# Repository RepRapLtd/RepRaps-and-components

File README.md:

# RepRaps-and-components
Various designs for RepRaps and bits of them

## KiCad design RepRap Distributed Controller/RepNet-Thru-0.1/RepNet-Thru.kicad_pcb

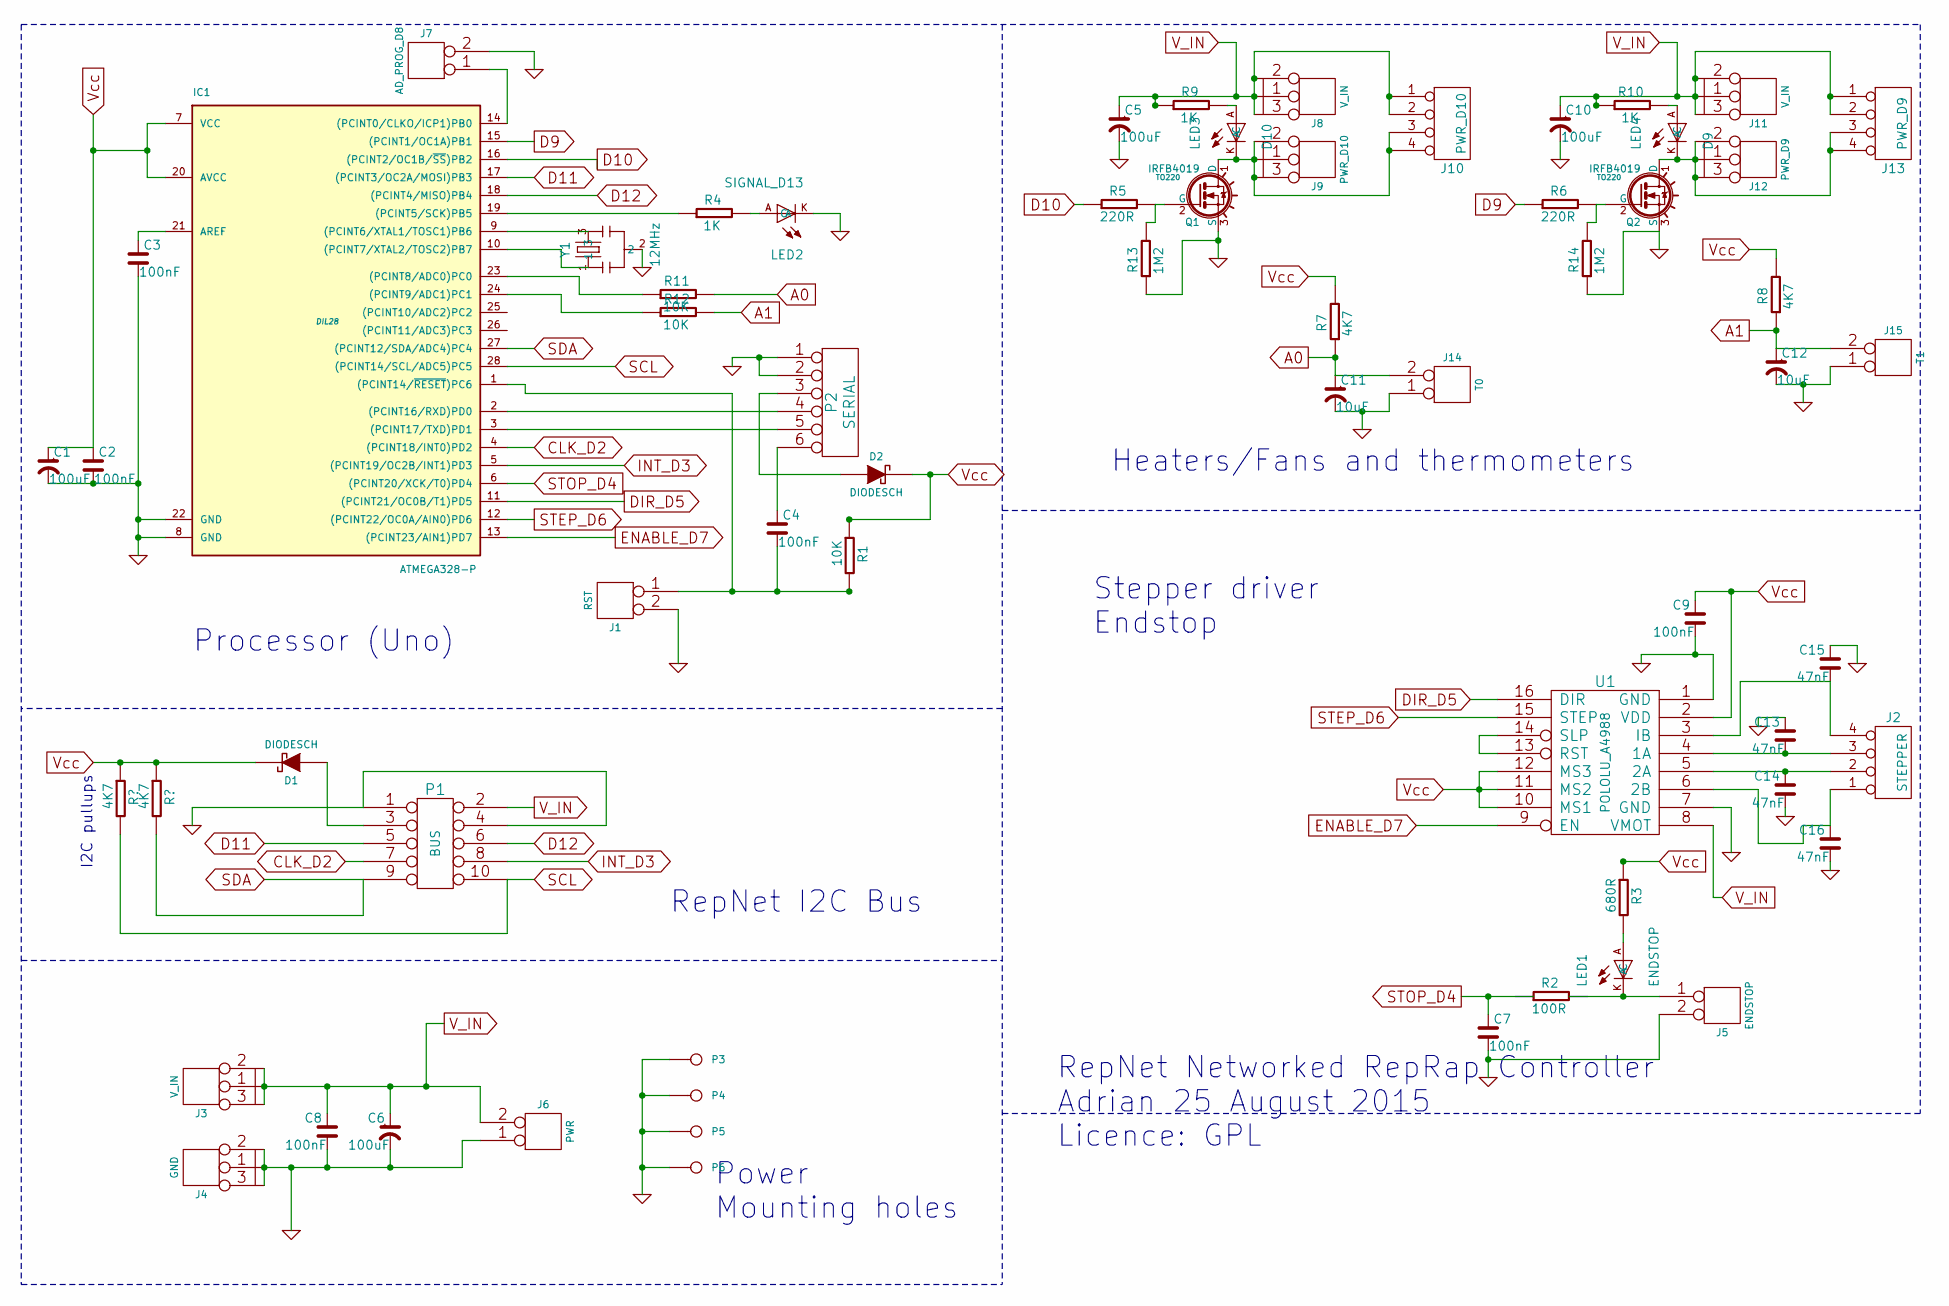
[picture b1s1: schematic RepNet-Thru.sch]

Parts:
C1, C5, C6, C10: 100uF
C2, C3, C4, C7, C8, C9: 100nF
C11, C12: 10uF
C13, C14, C15, C16: 47nF
D1, D2: DIODESCH
IC1: ATMEGA328-P; DIL28
J1: RST
J2: STEPPER
J3, J8, J11: V_IN
J4: GND
J5: ENDSTOP
J6: PWR
J7: AD_PROG_D8
J9, J10: PWR_D10
J12, J13: PWR_D9
J14: T0
J15: T1
LED1: ENDSTOP; SparkFun-LED3MM
LED2: SIGNAL_D13; SparkFun-LED3MM
LED3: D10; SparkFun-LED3MM
LED4: D9; SparkFun-LED3MM
P1: BUS
P2: SERIAL
P3, P4, P5, P6: mount
Q1, Q2: IRFB4019; TO220
R1, R11, R12: 10K
R2: 100R
R3: 680R
R4, R9, R10: 1K
R5, R6: 220R
R7, R8: 4K7
R13, R14: 1M2
U1: POLOLU_A4988
Y1: 12MHz; SparkFun-RESONATOR-PTH

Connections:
A0: C11.1, J14.2 (PM), R7.1, R11.2
A1: C12.1, J15.2 (PM), R8.1, R12.2
CLK_D2: IC1.4 ((PCINT18/INT0)PD2), P1.7
D9: IC1.15 ((PCINT1/OC1A)PB1), R6.1
D10: IC1.16 ((PCINT2/OC1B/~SS~)PB2), R5.1
D11: IC1.17 ((PCINT3/OC2A/MOSI)PB3), P1.5
D12: IC1.18 ((PCINT4/MISO)PB4), P1.6
DIR_D5: IC1.11 ((PCINT21/OC0B/T1)PD5), U1.16 (DIR)
ENABLE_D7: IC1.13 ((PCINT23/AIN1)PD7), U1.9 (EN)
GND: C1.2, C2.2, C3.2, C5.2, C6.2, C7.2, C8.2, C9.2, C10.2, C11.2, C12.2, C13.1, C14.2, C15.1, C16.2, IC1.8 (GND), IC1.22 (GND), J1.2 (PM), J4.1, J4.2, J4.3, J5.2 (PM), J6.1, J7.2 (PM), J14.1, J15.1, LED2.K (C), P1.1, P1.4, P2.1, P2.2, P3.1, P4.1, P5.1, P6.1, Q1.3 (S), Q2.3 (S), R13.1, R14.1, U1.1 (GND), U1.7 (GND), Y1.2
INT_D3: IC1.5 ((PCINT19/OC2B/INT1)PD3), P1.8
unnamed: IC1.10 ((PCINT7/XTAL2/TOSC2)PB7), Y1.1
unnamed: IC1.9 ((PCINT6/XTAL1/TOSC1)PB6), Y1.3
unnamed: IC1.3 ((PCINT17/TXD)PD1), P2.5
unnamed: IC1.2 ((PCINT16/RXD)PD0), P2.4
unnamed: D2.1 (A), P2.3
unnamed: IC1.14 ((PCINT0/CLKO/ICP1)PB0), J7.1
unnamed: C4.2, IC1.1 ((PCINT14/~RESET~)PC6), J1.1, R1.2
unnamed: C4.1, P2.6
unnamed: U1.13 (RST), U1.14 (SLP)
unnamed: C3.1, IC1.21 (AREF)
unnamed: D1.1 (A), P1.3
unnamed: LED2.A, R4.2
unnamed: IC1.19 ((PCINT5/SCK)PB5), R4.1
unnamed: LED1.A, R3.2
unnamed: C16.1, J2.1, U1.6 (2B)
unnamed: C15.2, J2.4, U1.3 (IB)
unnamed: LED4.A, R10.2
unnamed: LED3.A, R9.2
unnamed: Q1.2 (G), R5.2, R13.2
unnamed: Q2.2 (G), R6.2, R14.2
unnamed: IC1.23 ((PCINT8/ADC0)PC0), R11.1
unnamed: IC1.24 ((PCINT9/ADC1)PC1), R12.1
unnamed: J5.1, LED1.K (C)
unnamed: C13.2, J2.3, U1.4 (1A)
unnamed: C14.1, J2.2, U1.5 (2A)
unnamed: J9.1, J9.2, J9.3, J10.3, J10.4, LED3.K (C), Q1.1 (D)
unnamed: J12.1, J12.2, J12.3, J13.3, J13.4, LED4.K (C), Q2.1 (D)
SCL: IC1.28 ((PCINT14/SCL/ADC5)PC5), P1.10; also elsewhere on the board
SDA: IC1.27 ((PCINT12/SDA/ADC4)PC4), P1.9; also elsewhere on the board
STEP_D6: IC1.12 ((PCINT22/OC0A/AIN0)PD6), U1.15 (STEP)
STOP_D4: C7.1, IC1.6 ((PCINT20/XCK/T0)PD4)
V_IN: C5.1, C6.1, C8.1, C10.1, J3.1, J3.2, J3.3, J6.2 (PM), J8.1, J8.2, J8.3, J10.1, J10.2, J11.1, J11.2, J11.3, J13.1, J13.2, P1.2, R9.1, R10.1, U1.8 (VMOT)
Vcc: C1.1, C2.1, C9.1, D1.2 (K), D2.2 (K), IC1.7 (VCC), IC1.20 (AVCC), R1.1, R3.1, R7.2, R8.2, U1.2 (VDD), U1.10 (MS1), U1.11 (MS2), U1.12 (MS3); also elsewhere on the board

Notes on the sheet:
Processor (Uno)
RepNet I2C Bus
Power Mounting holes
Stepper driver Endstop
Heaters/Fans and thermometers
RepNet Networked RepRap Controller Adrian 25 August 2015 Licence: GPL
I2C pullups

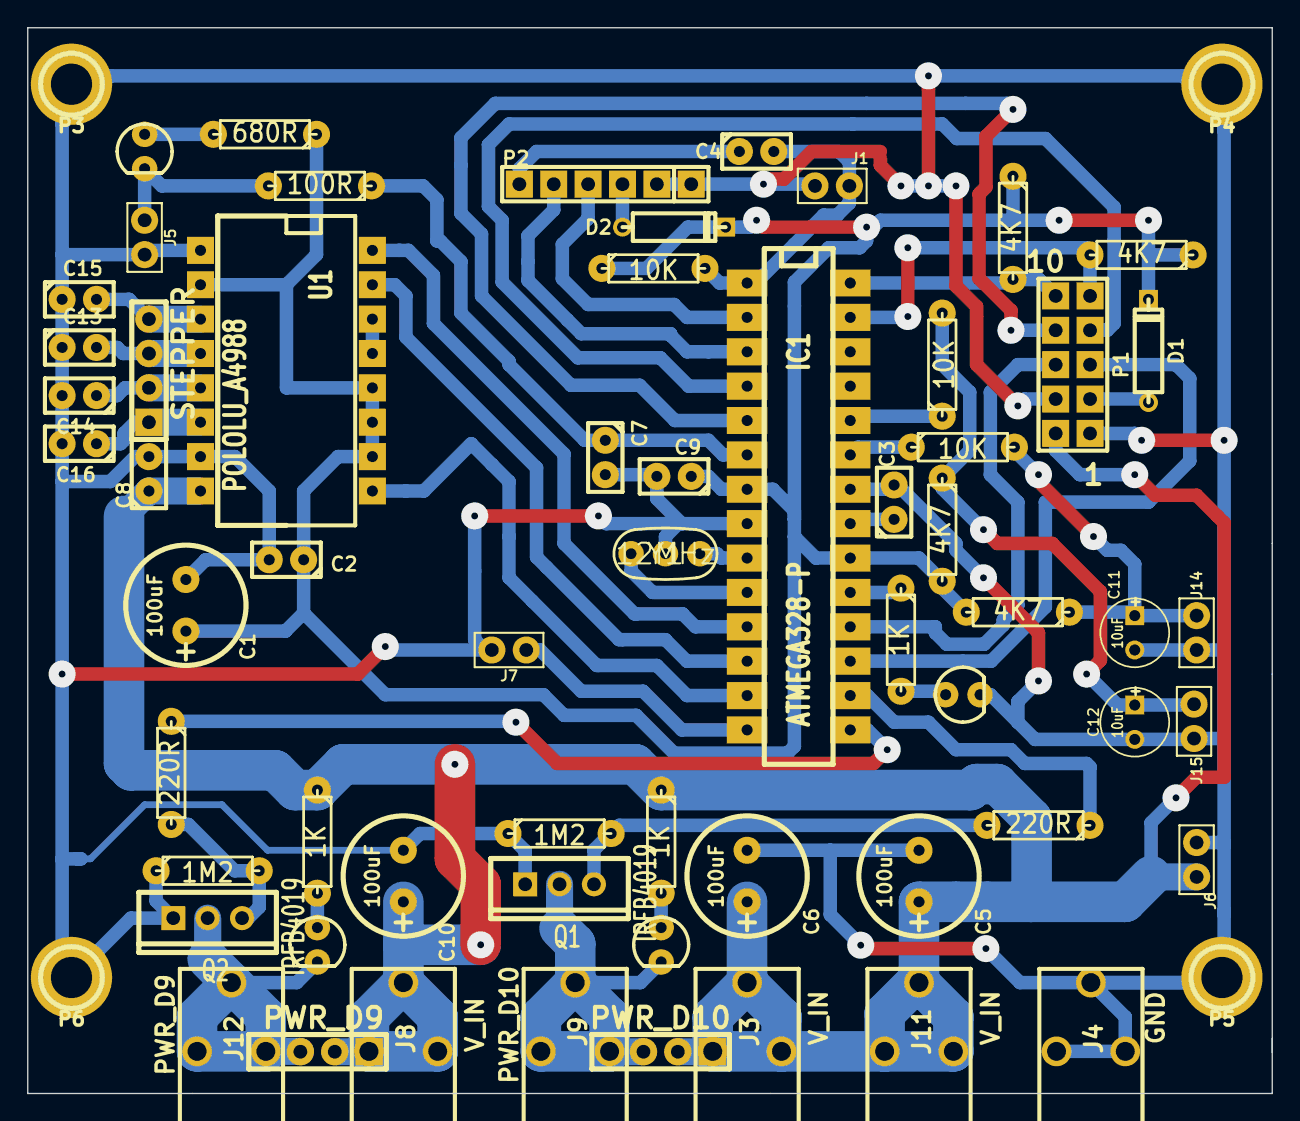
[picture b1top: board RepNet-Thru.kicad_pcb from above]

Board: 2 copper layers, 91.9 x 78.7 mm, 64 parts (0 on the bottom side), 44 nets.

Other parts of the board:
R15, R16: 4K7; R3

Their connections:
SCL: R15.2; also elsewhere on the board
SDA: R16.2; also elsewhere on the board
Vcc: R15.1, R16.1; also elsewhere on the board

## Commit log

2024-05-29 Updating...
